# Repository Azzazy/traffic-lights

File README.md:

# traffic-lights
Traffic lights demo project for Robotics Club AUC

## Requirments
An electrical board performing the functionalities of a traffic light. The funcationalities are:
- Red, Yellow and Green lights alternating in order
- Pass button to get Red faster
The board has a single source of power. 

## Design steps
- System block diagram
- Psudo code
- Circuit schematic
- Code
- Test setup
- Layout design
- Fabrication
- Live test

## Tools used
- [KiCAD](http://kicad-pcb.org/download/)
- [Arduino onlne](https://create.arduino.cc/)
- [Arduino simulator](https://www.tinkercad.com)

## Resources
- [Simulation](https://www.tinkercad.com/things/bBg1C2l9w1r-incredible-gogo-blorr/editel?sharecode=Yr4FscFQvJzt9poQF2iMoLLDoCD9sWlmrVRPqTrWZGg=)
- [Git course](https://www.lynda.com/Git-tutorials/Up-Running-Git-GitHub/409275-2.html)
- [Arduino specs](https://store.arduino.cc/usa/arduino-uno-rev3)
- [ATMEGA328 datasheet](http://ww1.microchip.com/downloads/en/DeviceDoc/ATmega48A-PA-88A-PA-168A-PA-328-P-DS-DS40002061A.pdf)
- [Arduino schematic](https://www.arduino.cc/en/uploads/Main/arduino-uno-schematic.pdf)

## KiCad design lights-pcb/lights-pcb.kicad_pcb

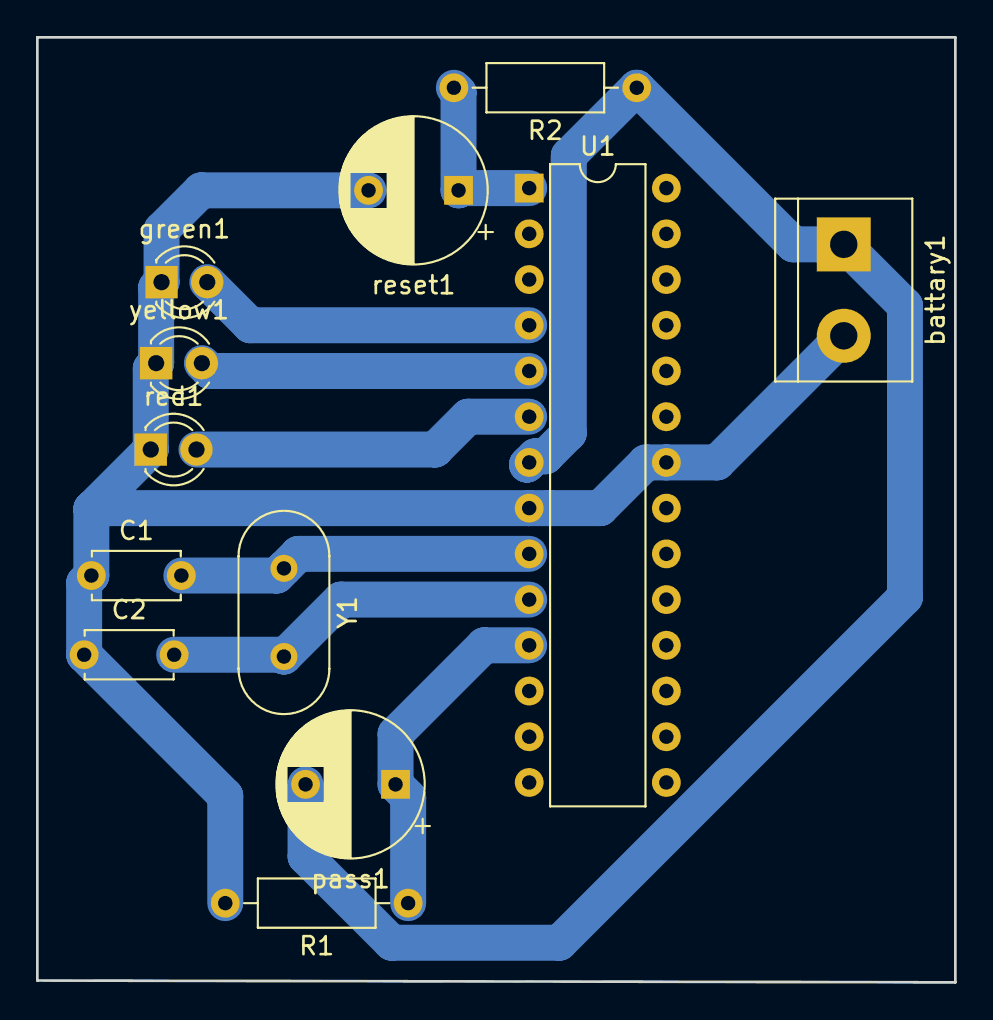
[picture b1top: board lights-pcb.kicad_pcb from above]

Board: 2 copper layers, 51.0 x 52.5 mm, 12 parts (0 on the bottom side), 9 nets.

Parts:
C1, C2: C; C_Disc_D4.7mm_W2.5mm_P5.00mm
R1, R2: R; R_Axial_DIN0207_L6.3mm_D2.5mm_P10.16mm_Horizontal
U1: ATmega328P-PU; DIP-28_W7.62mm
Y1: Crystal; Crystal_HC18-U_Vertical
battary1: Conn_01x02_Female; TerminalBlock_bornier-2_P5.08mm
green1: LED; LED_D3.0mm_Clear
pass1: SW_Push; CP_Radial_D8.0mm_P5.00mm
red1: LED; LED_D3.0mm
reset1: SW_Push; CP_Radial_D8.0mm_P5.00mm
yellow1: LED; LED_D3.0mm

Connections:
+5V: R2.1, U1.7, battary1.1, pass1.2
GND: C1.1, C2.1, R1.2, U1.8, U1.22, battary1.2, green1.1, red1.1, reset1.2, yellow1.1
unnamed: C1.2, U1.9, Y1.1
unnamed: C2.2, U1.10, Y1.2
unnamed: R1.1, U1.11, pass1.1
unnamed: R2.2, U1.1, reset1.1
unnamed: U1.4, green1.2
unnamed: U1.5, yellow1.2
unnamed: U1.6, red1.2

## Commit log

2019-04-04 add simulation
2019-04-09 add git course
2019-04-09 add resources
2019-04-11 KiCAD project
